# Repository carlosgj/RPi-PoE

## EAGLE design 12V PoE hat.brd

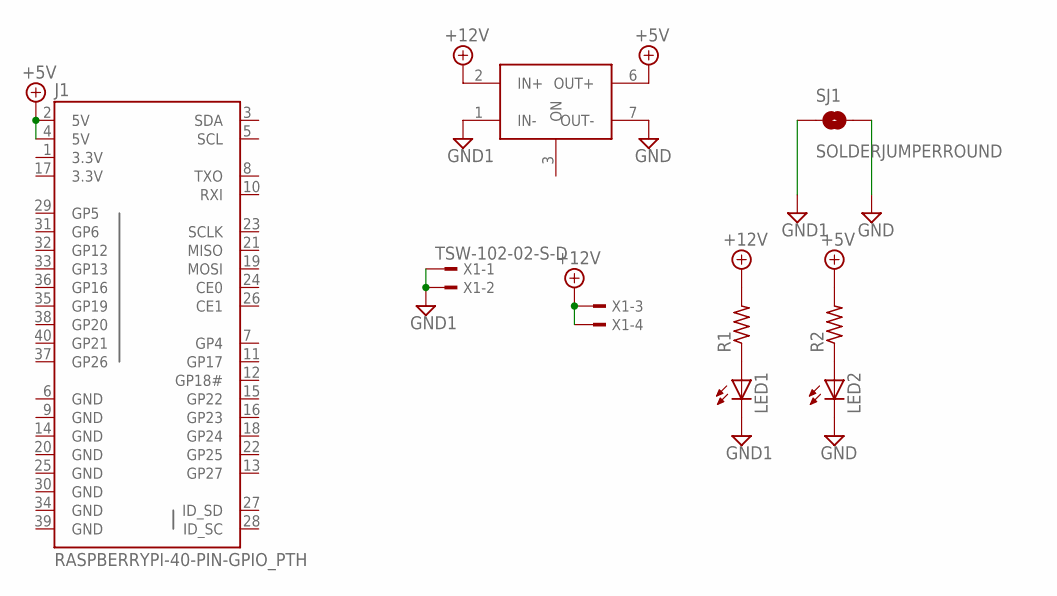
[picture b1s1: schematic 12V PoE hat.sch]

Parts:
J1: RASPBERRYPI-40-PIN-GPIO_PTH; 2X20_SHROUDED
LED1, LED2: LEDSMT1206; 1206
R1, R2: R-US_M1206; M1206
SJ1: SOLDERJUMPERROUND; SJ_ROUND
U$1: SPBW06F-05; SIL08A
X1: TSW-102-02-S-D

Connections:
3.3V: J1.1 (3.3V), J1.17 (3.3V)
+5V: J1.2 (5V), J1.4 (5V), R2.2, U$1.6 (OUT+)
+12V: R1.2, U$1.2 (IN+), X1.3, X1.4
GND: J1.6 (GND), J1.9 (GND), J1.14 (GND), J1.20 (GND), J1.25 (GND), J1.30 (GND), J1.34 (GND), J1.39 (GND), LED2.C, SJ1.2, U$1.7 (OUT-)
GND1: LED1.C, SJ1.1, U$1.1 (IN-), X1.1, X1.2
unnamed: LED1.A, R1.1
unnamed: LED2.A, R2.1

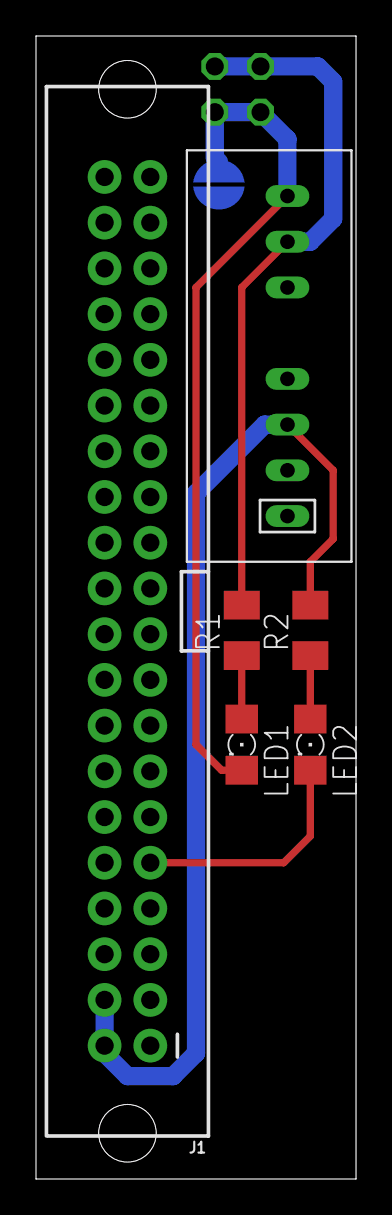
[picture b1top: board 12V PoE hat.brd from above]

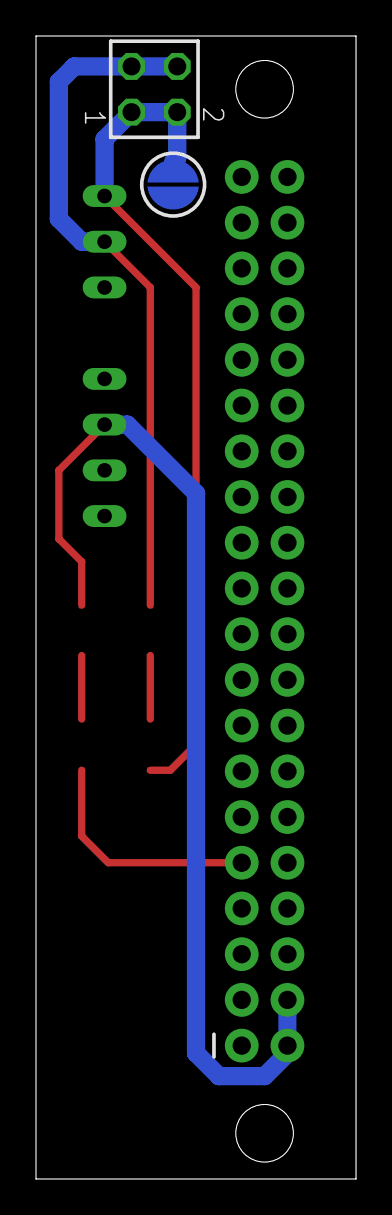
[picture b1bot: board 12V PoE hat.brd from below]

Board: 2 copper layers, 17.8 x 63.5 mm, 8 parts (2 on the bottom side), 7 nets.

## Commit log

2018-07-24 Initial design

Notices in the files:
parts and their libraries:
SparkFun-Connectors: Licensing: Creative Commons ShareAlike 4.0 International - https://creativecommons.org/licenses/by-sa/4.0
